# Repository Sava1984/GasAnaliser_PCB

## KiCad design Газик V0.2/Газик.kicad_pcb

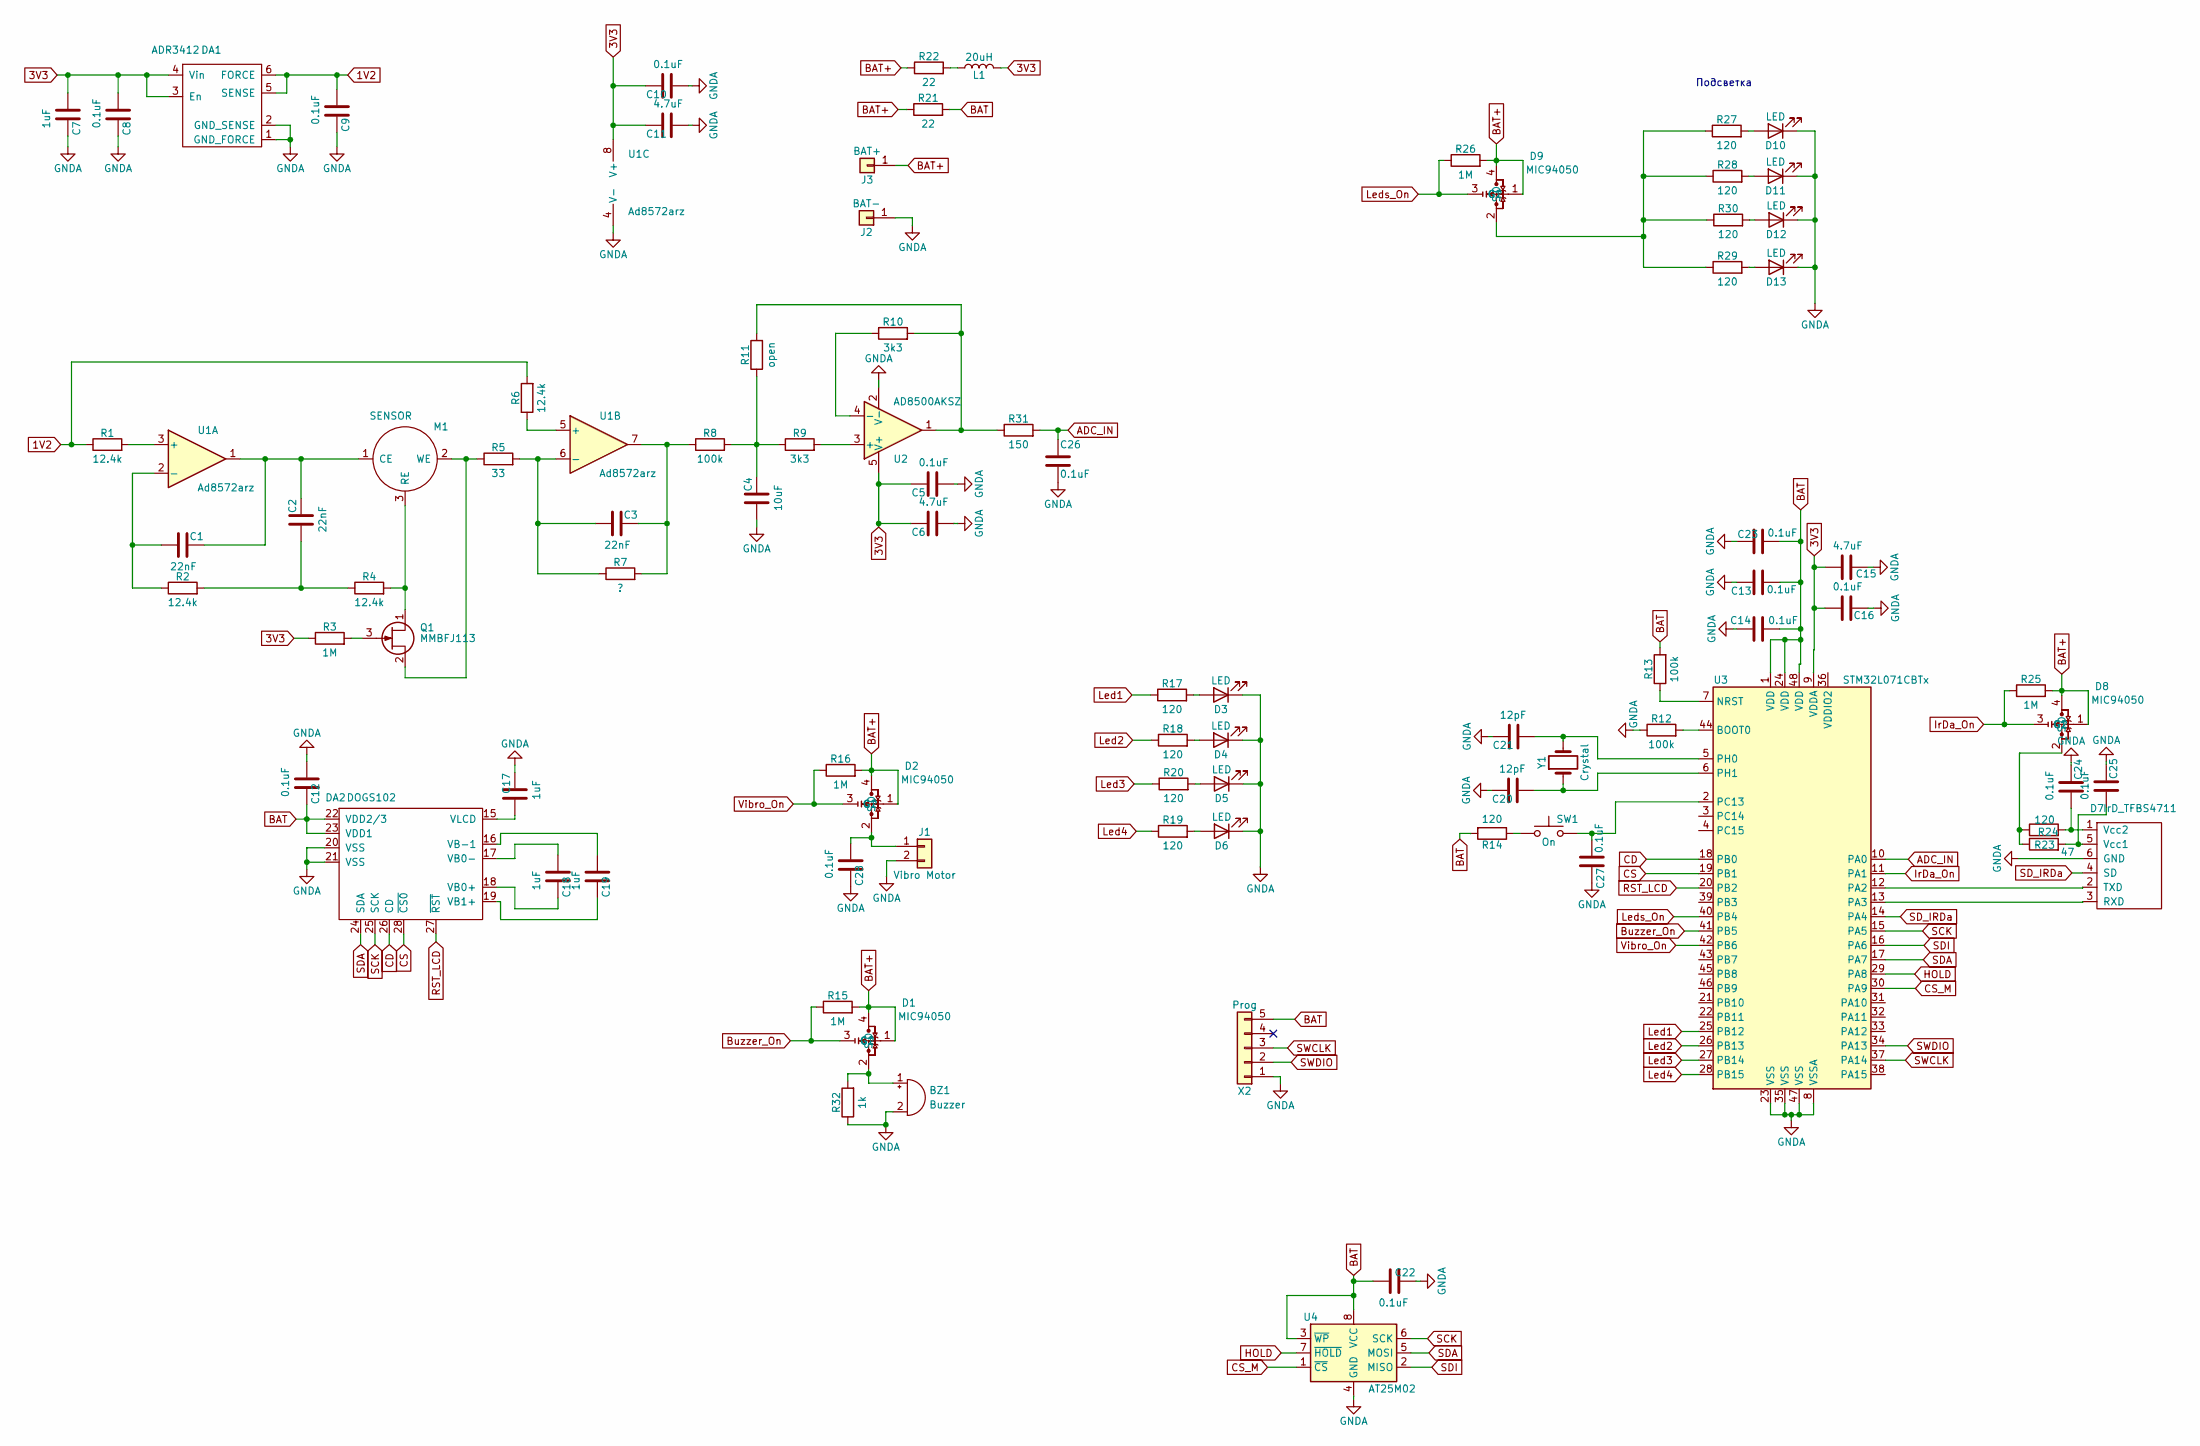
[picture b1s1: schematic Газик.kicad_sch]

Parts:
BZ1: Buzzer; Part Number SD1209T3-A1
C1, C2: 22nF; C_0603_1608Metric; Part Number 06035C223KAZ2A 22nF
C3: 22nF; C_0805_2012Metric; Part Number GRM216R71H223KA01D 22nF
C4: 10uF; C_0805_2012Metric; Part Number JMK212BJ106MG-T 10uF
C5, C8, C9, C10, C12, C13, C14, C16, C22, C23, C24, C25, C26, C27, C28: 0.1uF; C_0603_1608Metric; Part Number C0603C104K4RAC 0.1uF
C6, C11, C15: 4.7uF; C_0805_2012Metric; Part Number GRM21BR61E475KA12L 4.7uF
C7, C17, C18, C19: 1uF; C_0603_1608Metric; Part Number GRM188R61C105KA93D 1uF
C20, C21: 12pF; C_0603_1608Metric; Part Number C0603C120K9RAC7411 12pF
D1, D2, D8, D9: MIC94050; SOT-143; Part Number MIC94050
D3, D4, D5, D6, D10, D11, D12, D13: LED; LED_1210_3225Metric; Part Number 2512_RED
D7: IrD_TFBS4711; TFBS4711; Part Number TFBS4711
DA1: ADR3412; SOT-23-6; Part Number ADR3412ARJZ
DA2: DOGS102; EA-DOGS102W-6; Part Number DOGS102
J1: Vibro Motor; PinHeader_1x02_P2.54mm_Vertical
J2: BAT-; PAD_5_5
J3: BAT+; PAD_5_5
L1: 20uH; L_0805_2012Metric; Part Number BLM21PG331SN1D
M1: SENSOR; CO; Part Number Sensor
Q1: MMBFJ113; SOT-23; Part Number MMBFJ113
R1, R2, R4, R6: 12.4k; R_0603_1608Metric; Part Number ERJ-3EKF1242V 12.4k
R3, R15, R16, R25, R26: 1M; R_0603_1608Metric; Part Number 1M
R5: 33; R_0603_1608Metric; Part Number MC 0.063W 0603 1% 33R.
R7: ?; R_0603_1608Metric; Part Number ERJ-3EKF1242V 12.4k
R8, R12, R13: 100k; R_0603_1608Metric; Part Number 100k
R9, R10: 3k3; R_0603_1608Metric; Part Number MC 0.063W 0603 1% 3K3.
R11: open; R_0603_1608Metric; Part Number MC 0.063W 0603 1% 3K3.
R14: 120; R_0603_1608Metric; Part Number 120
R17, R18, R19, R20, R24, R27, R28, R29, R30: 120; R_0603_1608Metric; Part Number MC 0.063W 0603 1% 33R.
R21, R22: 22; R_2512_6332Metric; Part Number CRGCQ2512J22R 22
R23: 47; R_0603_1608Metric; Part Number RCS060347R0FKEA 47
R31: 150; R_0603_1608Metric; Part Number MC 0.063W 0603 1% 3K3.
R32: 1k; R_0603_1608Metric; Part Number 1k
SW1: On; SW_SPST_CK_RS282G05A3; Part Number 1
U1: Ad8572arz; SO-8_3.9x4.9mm_P1.27mm; Part Number Ad8572arz
U2: AD8500AKSZ; TSOT-23-5; Part Number AD8500AKSZ
U3: STM32L071CBTx; LQFP-48_7x7mm_P0.5mm
U4: AT25M02; SO-8_3.9x4.9mm_P1.27mm; Part Number AT25M02
X2: Prog; PinHeader_1x05_P2.54mm_Vertical; Part number PLS-5
Y1: Crystal; Crystal_SMD_2012-2Pin_2.0x1.2mm; Part Number NX3215SA-32.768K

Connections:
1V2: C9.1, DA1.5 (SENSE), DA1.6 (FORCE), R1.1, R6.2
3V3: C5.2, C6.2, C7.1, C8.1, C10.2, C11.2, C15.2, C16.2, DA1.3 (En), DA1.4 (Vin), L1.2, R3.1, U1.8 (V+), U2.5 (V+), U3.9 (VDDA)
ADC_IN: C26.1, R31.2, U3.10 (PA0)
BAT: C12.2, C13.1, C14.1, C22.1, C23.1, DA2.22 (VDD2/3), DA2.23 (VDD1), R13.2, R14.2, R21.2, U3.1 (VDD), U3.24 (VDD), U3.48 (VDD), U4.3 (~WP), U4.8 (VCC), X2.5
BAT+: D1.1 (G1), D1.4 (D), D2.1 (G1), D2.4 (D), D8.1 (G1), D8.4 (D), D9.1 (G1), D9.4 (D), J3.1, R15.2, R16.2, R21.1, R22.1, R25.2, R26.2
Buzzer_On: D1.3 (G2), R15.1, U3.41 (PB5)
CD: DA2.26 (CD), U3.18 (PB0)
CS: DA2.28 (~CS0), U3.19 (PB1)
CS_M: U3.30 (PA9), U4.1 (~CS)
GNDA: BZ1.2 (+), C4.1, C5.1, C6.1, C7.2, C8.2, C9.2, C10.1, C11.1, C12.1, C13.2, C14.2, C15.1, C16.1, C17.2, C20.2, C21.2, C22.2, C23.2, C24.1, C25.1, C26.2, C27.2, C28.2, D3.1 (K), D4.1 (K), D5.1 (K), D6.1 (K), D7.6 (GND), D10.1 (K), D11.1 (K), D12.1 (K), D13.1 (K), DA1.1 (GND_FORCE), DA1.2 (GND_SENSE), DA2.20 (VSS), DA2.21 (VSS), J1.2, J2.1, R12.1, R32.1, U1.4 (V-), U2.2 (V-), U3.8 (VSSA), U3.23 (VSS), U3.35 (VSS), U3.47 (VSS), U4.4 (GND), X2.1
HOLD: U3.29 (PA8), U4.7 (~HOLD)
IrDa_On: D8.3 (G2), R25.1, U3.11 (PA1)
Led1: R17.1, U3.25 (PB12)
Led2: R18.1, U3.26 (PB13)
Led3: R20.1, U3.27 (PB14)
Led4: R19.1, U3.28 (PB15)
Leds_On: D9.3 (G2), R26.1, U3.40 (PB4)
unnamed: BZ1.1 (-), D1.2 (S), R32.2
unnamed: C1.1, R2.1, U1.2 (-)
unnamed: C1.2, C2.2, M1.1 (CE), U1.1
unnamed: C2.1, R2.2, R4.1
unnamed: C3.1, R5.2, R7.1, U1.6 (-)
unnamed: C3.2, R7.2, R8.1, U1.7
unnamed: C4.2, R8.2, R9.1, R11.1
unnamed: C17.1, DA2.15 (VLCD)
unnamed: C18.1, DA2.17 (VB0-)
unnamed: C18.2, DA2.18 (VB0+)
unnamed: C19.1, DA2.16 (VB-1)
unnamed: C19.2, DA2.19 (VB1+)
unnamed: C20.1, U3.6 (PH1), Y1.1
unnamed: C21.1, U3.5 (PH0), Y1.2
unnamed: C24.2, D7.1 (Vcc2), R24.2
unnamed: C25.2, D7.5 (Vcc1), R23.2
unnamed: C28.1, D2.2 (S), J1.1
unnamed: D3.2 (A), R17.2
unnamed: D4.2 (A), R18.2
unnamed: D5.2 (A), R20.2
unnamed: D6.2 (A), R19.2
unnamed: D7.2 (TXD), U3.12 (PA2)
unnamed: D7.3 (RXD), U3.13 (PA3)
unnamed: D8.2 (S), R23.1, R24.1
unnamed: D9.2 (S), R27.1, R28.1, R29.1, R30.1
unnamed: D10.2 (A), R27.2
unnamed: D11.2 (A), R28.2
unnamed: D12.2 (A), R30.2
unnamed: D13.2 (A), R29.2
unnamed: L1.1, R22.2
unnamed: M1.2 (WE), Q1.2 (S), R5.1
unnamed: M1.3 (RE), Q1.1 (D), R4.2
unnamed: Q1.3 (G), R3.2
unnamed: R1.2, U1.3 (+)
unnamed: R6.1, U1.5 (+)
unnamed: R9.2, U2.3 (+)
unnamed: R10.1, U2.4 (-)
unnamed: R10.2, R11.2, R31.1, U2.1
unnamed: R12.2, U3.44 (BOOT0)
unnamed: R13.1, U3.7 (NRST)
unnamed: R14.1, SW1.1
unnamed: C27.1, SW1.2, U3.2 (PC13)
RST_LCD: DA2.27 (~RST), U3.20 (PB2)
SCK: DA2.25 (SCK), U3.15 (PA5), U4.6 (SCK)
SDA: DA2.24 (SDA), U3.17 (PA7), U4.5 (MOSI)
SDI: U3.16 (PA6), U4.2 (MISO)
SD_IRDa: D7.4 (SD), U3.14 (PA4)
SWCLK: U3.37 (PA14), X2.3
SWDIO: U3.34 (PA13), X2.2
Vibro_On: D2.3 (G2), R16.1, U3.42 (PB6)

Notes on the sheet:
Подсветка

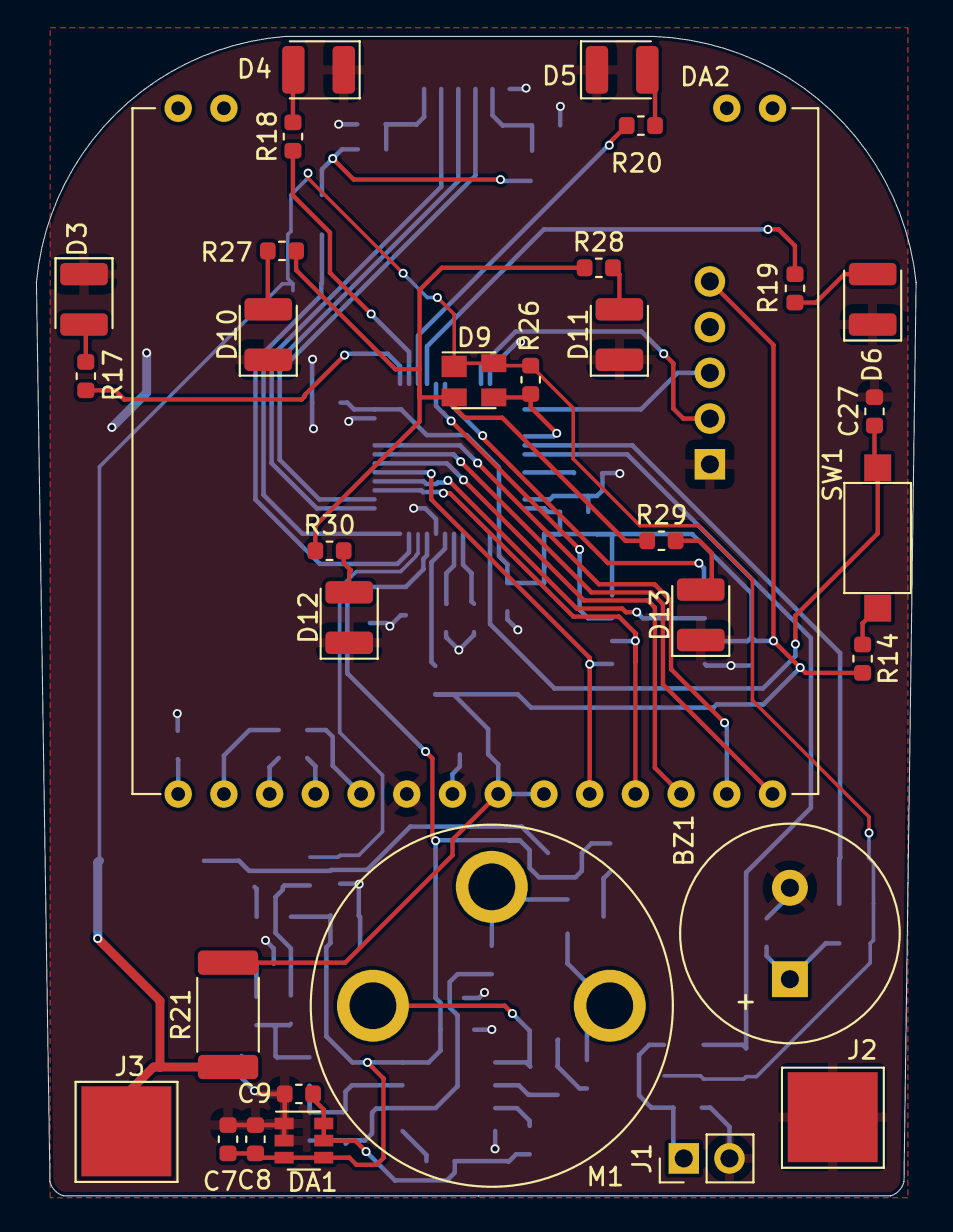
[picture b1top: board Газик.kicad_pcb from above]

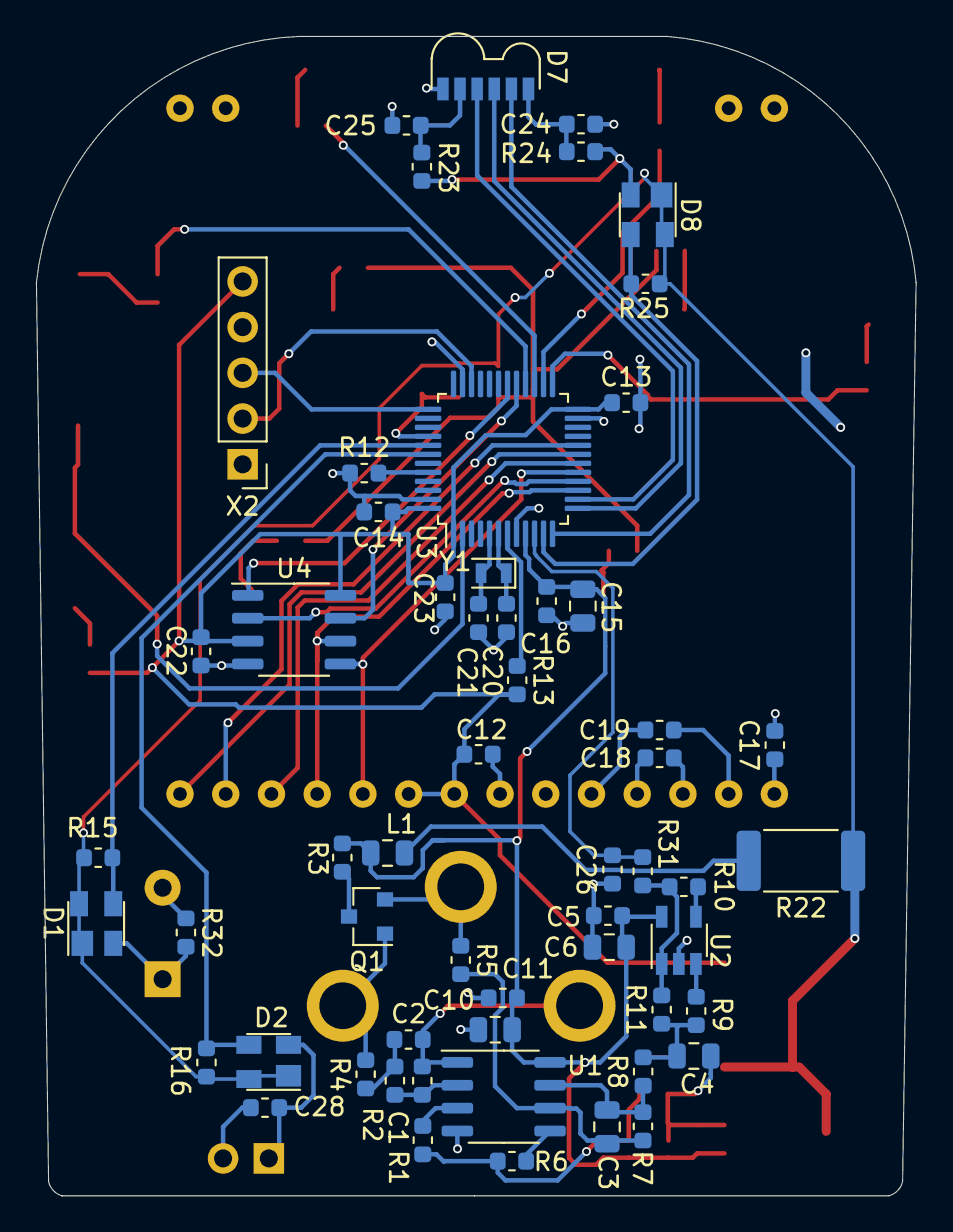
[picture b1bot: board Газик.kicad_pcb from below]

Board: 2 copper layers, 48.9 x 64.4 mm, 89 parts (57 on the bottom side), 67 nets.

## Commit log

2021-09-16 1 commit
2021-09-16 Изvенен gitignore
